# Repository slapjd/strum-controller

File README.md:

# Strum Controller PCB
WIP replacement combined strum PCB and microcontroller for use with [Guitar Configurator](https://github.com/sanjay900/guitar-configurator)

Requires [kicad-lib-rp2040](https://github.com/arnytrty-net/kicad-lib-rp2040) installed within your kicad setup

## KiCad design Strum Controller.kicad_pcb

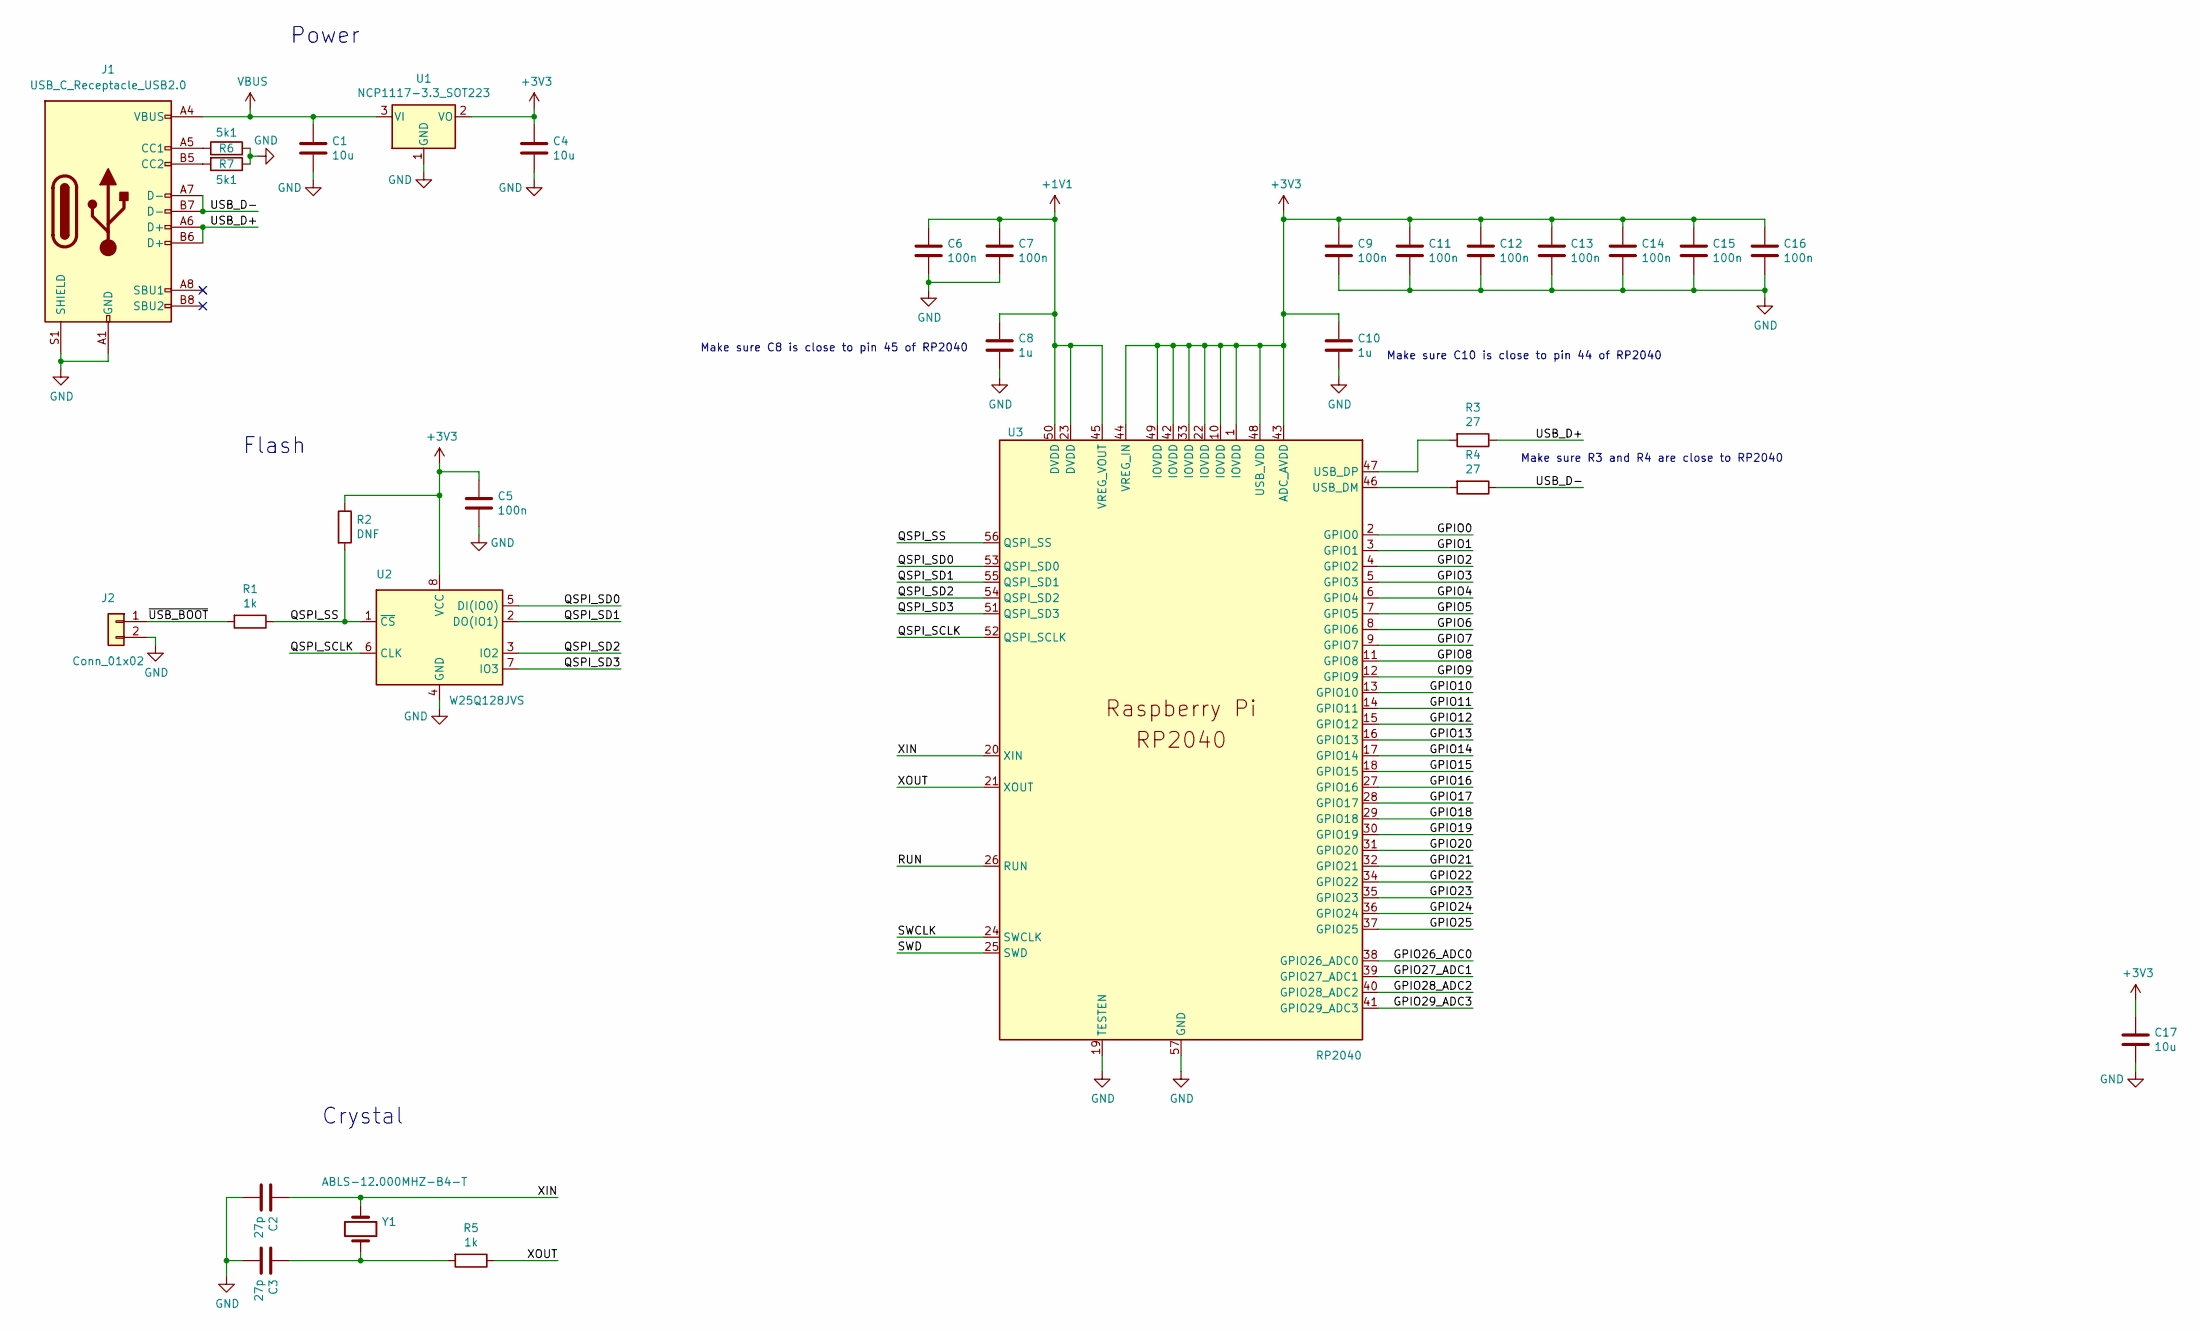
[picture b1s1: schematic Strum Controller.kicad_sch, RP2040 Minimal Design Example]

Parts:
C1, C4, C17: 10u; C_0805_2012Metric
C2, C3: 27p; C_0402_1005Metric
C5, C6, C7, C9, C11, C12, C13, C14, C15, C16: 100n; C_0402_1005Metric
C8, C10: 1u; C_0402_1005Metric
J1: USB_C_Receptacle_USB2.0; USB_C_Receptacle_JAE_DX07S016JA1R1500
J2: Conn_01x02; PinHeader_1x02_P2.54mm_Vertical
R1, R5: 1k; R_0402_1005Metric
R2: DNF; R_0402_1005Metric
R3, R4: 27; R_0402_1005Metric
R6, R7: 5k1; R_0402_1005Metric
U1: NCP1117-3.3_SOT223; SOT-223-3_TabPin2
U2: W25Q128JVS; SOIC-8_5.275x5.275mm_P1.27mm
U3: RP2040; QFN-56_EP_7x7_Pitch0.4mm_ThermalVias
Y1: ABLS-12.000MHZ-B4-T; Crystal_SMD_HC49-SD

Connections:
+1V1: C6.1, C7.1, C8.1, U3.23 (DVDD), U3.45 (VREG_VOUT), U3.50 (DVDD)
+3V3: C4.1, C5.1, C9.1, C10.1, C11.1, C12.1, C13.1, C14.1, C15.1, C16.1, C17.1, R2.1, U1.2 (VO), U2.8 (VCC), U3.1 (IOVDD), U3.10 (IOVDD), U3.22 (IOVDD), U3.33 (IOVDD), U3.42 (IOVDD), U3.43 (ADC_AVDD), U3.44 (VREG_IN), U3.48 (USB_VDD), U3.49 (IOVDD)
/GPIO0: U3.2 (GPIO0)
/GPIO1: U3.3 (GPIO1)
/GPIO2: U3.4 (GPIO2)
/GPIO3: U3.5 (GPIO3)
/GPIO4: U3.6 (GPIO4)
/GPIO5: U3.7 (GPIO5)
/GPIO6: U3.8 (GPIO6)
/GPIO7: U3.9 (GPIO7)
/GPIO8: U3.11 (GPIO8)
/GPIO9: U3.12 (GPIO9)
/GPIO10: U3.13 (GPIO10)
/GPIO11: U3.14 (GPIO11)
/GPIO12: U3.15 (GPIO12)
/GPIO13: U3.16 (GPIO13)
/GPIO14: U3.17 (GPIO14)
/GPIO15: U3.18 (GPIO15)
/GPIO16: U3.27 (GPIO16)
/GPIO17: U3.28 (GPIO17)
/GPIO18: U3.29 (GPIO18)
/GPIO19: U3.30 (GPIO19)
/GPIO20: U3.31 (GPIO20)
/GPIO21: U3.32 (GPIO21)
/GPIO22: U3.34 (GPIO22)
/GPIO23: U3.35 (GPIO23)
/GPIO24: U3.36 (GPIO24)
/GPIO25: U3.37 (GPIO25)
/GPIO26_ADC0: U3.38 (GPIO26_ADC0)
/GPIO27_ADC1: U3.39 (GPIO27_ADC1)
/GPIO28_ADC2: U3.40 (GPIO28_ADC2)
/GPIO29_ADC3: U3.41 (GPIO29_ADC3)
/QSPI_SCLK: U2.6 (CLK), U3.52 (QSPI_SCLK)
/QSPI_SD0: U2.5 (DI(IO0)), U3.53 (QSPI_SD0)
/QSPI_SD1: U2.2 (DO(IO1)), U3.55 (QSPI_SD1)
/QSPI_SD2: U2.3 (IO2), U3.54 (QSPI_SD2)
/QSPI_SD3: U2.7 (IO3), U3.51 (QSPI_SD3)
/QSPI_SS: R1.1, R2.2, U2.1 (~CS), U3.56 (QSPI_SS)
/RUN: U3.26 (RUN)
/SWCLK: U3.24 (SWCLK)
/SWD: U3.25 (SWD)
/USB_D+: J1.A6 (D+), J1.B6 (D+), R3.1
/USB_D-: J1.A7 (D-), J1.B7 (D-), R4.1
/XIN: C2.1, U3.20 (XIN), Y1.1
/XOUT: R5.1, U3.21 (XOUT)
/~USB_BOOT: J2.1, R1.2
GND: C1.2, C2.2, C3.2, C4.2, C5.2, C6.2, C7.2, C8.2, C9.2, C10.2, C11.2, C12.2, C13.2, C14.2, C15.2, C16.2, C17.2, J1.A1 (GND), J1.A12 (GND), J1.B1 (GND), J1.B12 (GND), J1.S1 (SHIELD), J2.2, R6.2, R7.1, U1.1 (GND), U2.4 (GND), U3.19 (TESTEN), U3.57 (GND)
unnamed: C3.1, R5.2, Y1.2
unnamed: J1.A5 (CC1), R6.1
unnamed: J1.B5 (CC2), R7.2
unnamed: R4.2, U3.46 (USB_DM)
unnamed: R3.2, U3.47 (USB_DP)
VBUS: C1.1, J1.A4 (VBUS), J1.A9 (VBUS), J1.B4 (VBUS), J1.B9 (VBUS), U1.3 (VI)

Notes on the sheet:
Make sure C10 is close to pin 44 of RP2040
Power
Crystal
Make sure C8 is close to pin 45 of RP2040
Flash
Make sure R3 and R4 are close to RP2040

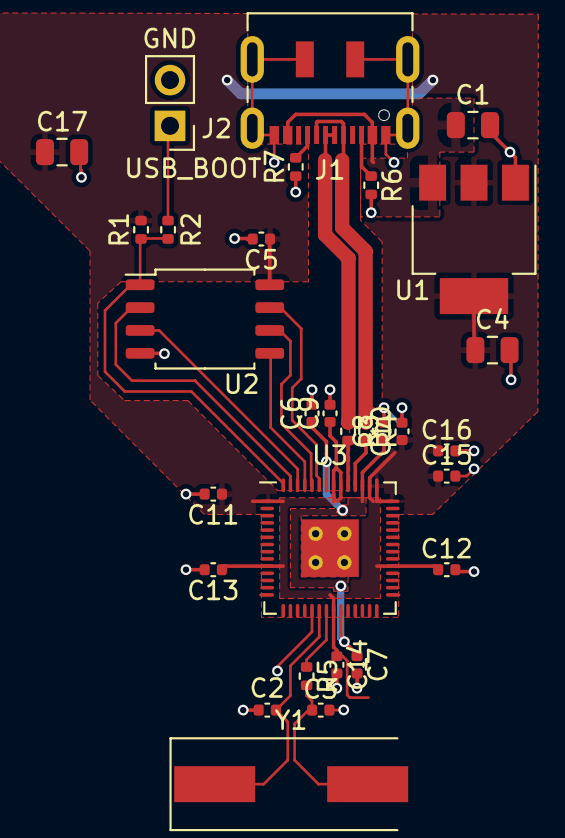
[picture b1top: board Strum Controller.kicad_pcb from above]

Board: 2 copper layers, 30 parts (0 on the bottom side), 20 nets.

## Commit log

2022-03-11 Added RP2040 + USB-C
2022-05-04 Restart design using modified RP2040 minimal design from RasPi Foundation
2022-05-04 Move to proper RP2040 library
2022-05-04 README file
